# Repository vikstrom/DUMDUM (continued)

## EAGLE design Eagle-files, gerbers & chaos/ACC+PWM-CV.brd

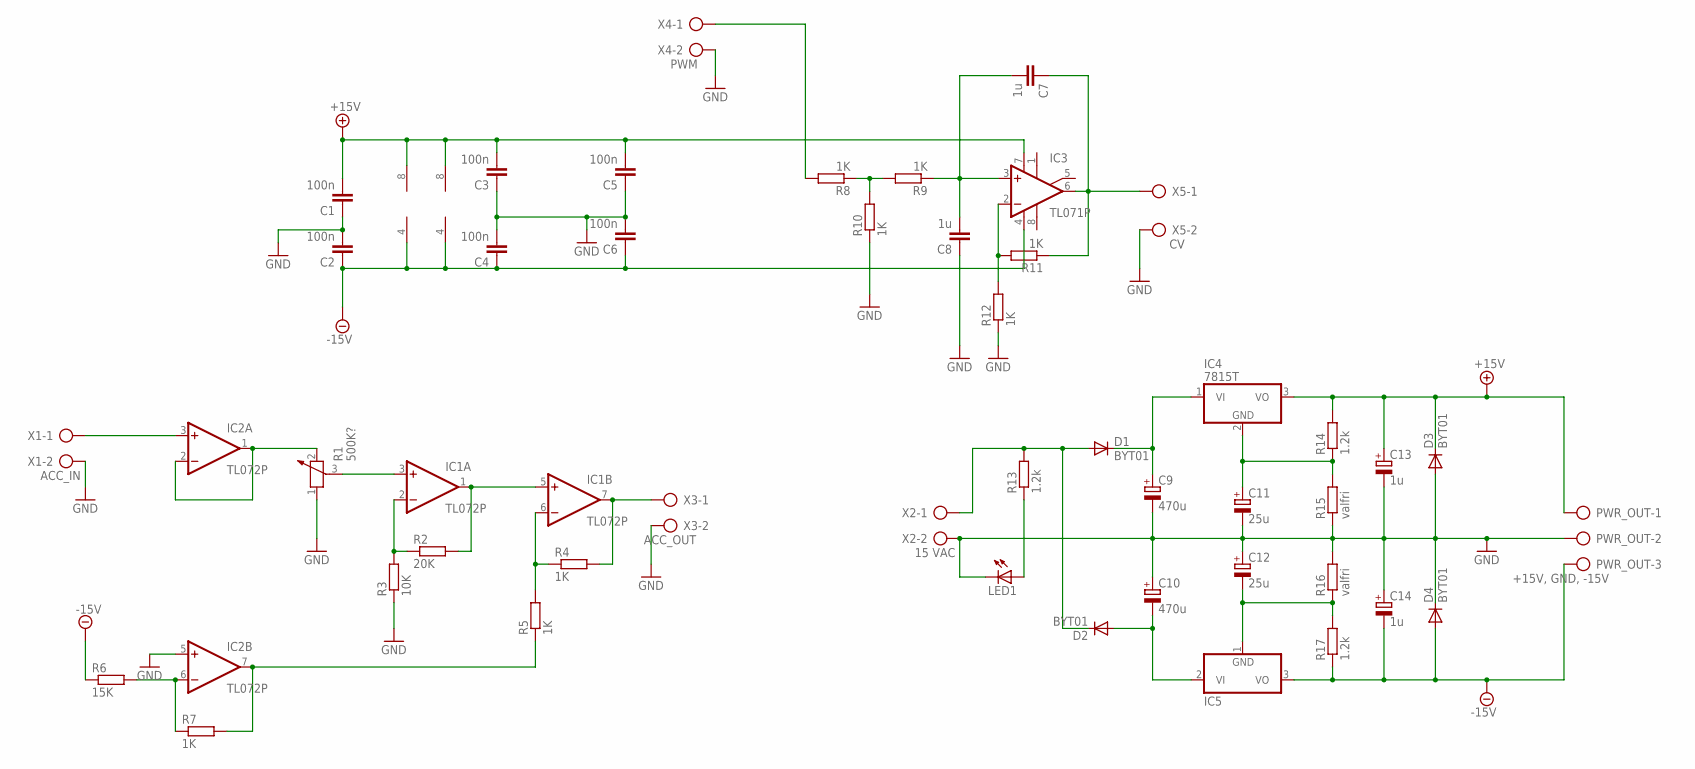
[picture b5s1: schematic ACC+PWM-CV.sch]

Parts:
C1, C2, C3, C4, C5, C6: 100n; C075-042X103
C7, C8: 1u; C075-042X103
C9, C10: 470u; E5-6
C11, C12: 25u; E5-6
C13, C14: 1u; E5-6
D1, D2, D3, D4: BYT01; F126-10
IC1, IC2: TL072P; DIL08
IC3: TL071P; DIL08
IC4: 7815T; TO220H
IC5: 7915T; TO220H
LED1: LED5MM
PWR_OUT: +15V, GND, -15V; AK300/3
R1: 500K?; PT-10
R2: 20K; 0207/10
R3: 10K; 0207/10
R4, R5, R7, R8, R9, R10, R11, R12: 1K; 0207/10
R6: 15K; 0207/10
R13, R14, R17: 1.2k; 0207/10
R15, R16: valfri; 0207/10
X1: ACC_IN; AK300/2
X2: 15 VAC; AK300/2
X3: ACC_OUT; AK300/2
X4: PWM; AK300/2
X5: CV; AK300/2

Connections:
+15V: C1.2, C3.2, C5.2, C13.+, D3.C, IC1.8 (V+), IC2.8 (V+), IC3.7 (V+), IC4.3 (VO), PWR_OUT.1, R14.2
-15V: C2.1, C4.1, C6.1, C14.-, D4.A, IC1.4 (V-), IC2.4 (V-), IC3.4 (V-), IC5.3 (VO), PWR_OUT.3, R6.1, R17.1
GND: C1.1, C2.2, C3.1, C4.2, C5.1, C6.2, C8.1, C9.-, C10.+, C11.-, C12.+, C13.-, C14.+, D3.A, D4.C, IC2.5 (+IN), LED1.K (C), PWR_OUT.2, R1.1, R3.1, R10.1, R12.1, R15.1, R16.2, X1.2, X2.2, X3.2, X4.2, X5.2
unnamed: IC2.1 (OUT), IC2.2 (-IN), R1.2
unnamed: IC1.3 (+IN), R1.3
unnamed: IC1.1 (OUT), IC1.5 (+IN), R2.2
unnamed: IC1.2 (-IN), R2.1, R3.2
unnamed: IC2.7 (OUT), R5.1, R7.2
unnamed: IC2.6 (-IN), R6.2, R7.1
unnamed: IC1.6 (-IN), R4.1, R5.2
unnamed: IC1.7 (OUT), R4.2, X3.1
unnamed: IC2.3 (+IN), X1.1
unnamed: R8.2, X4.1
unnamed: R8.1, R9.2, R10.2
unnamed: C7.2, C8.2, IC3.3 (+IN), R9.1
unnamed: C7.1, IC3.6 (OUT), R11.1, X5.1
unnamed: IC3.2 (-IN), R11.2, R12.2
unnamed: D1.A, D2.C, R13.2, X2.1
unnamed: LED1.A, R13.1
unnamed: C9.+, D1.C, IC4.1 (VI)
unnamed: C10.-, D2.A, IC5.2 (VI)
unnamed: C11.+, IC4.2 (GND), R14.1, R15.2
unnamed: C12.-, IC5.1 (GND), R16.1, R17.2

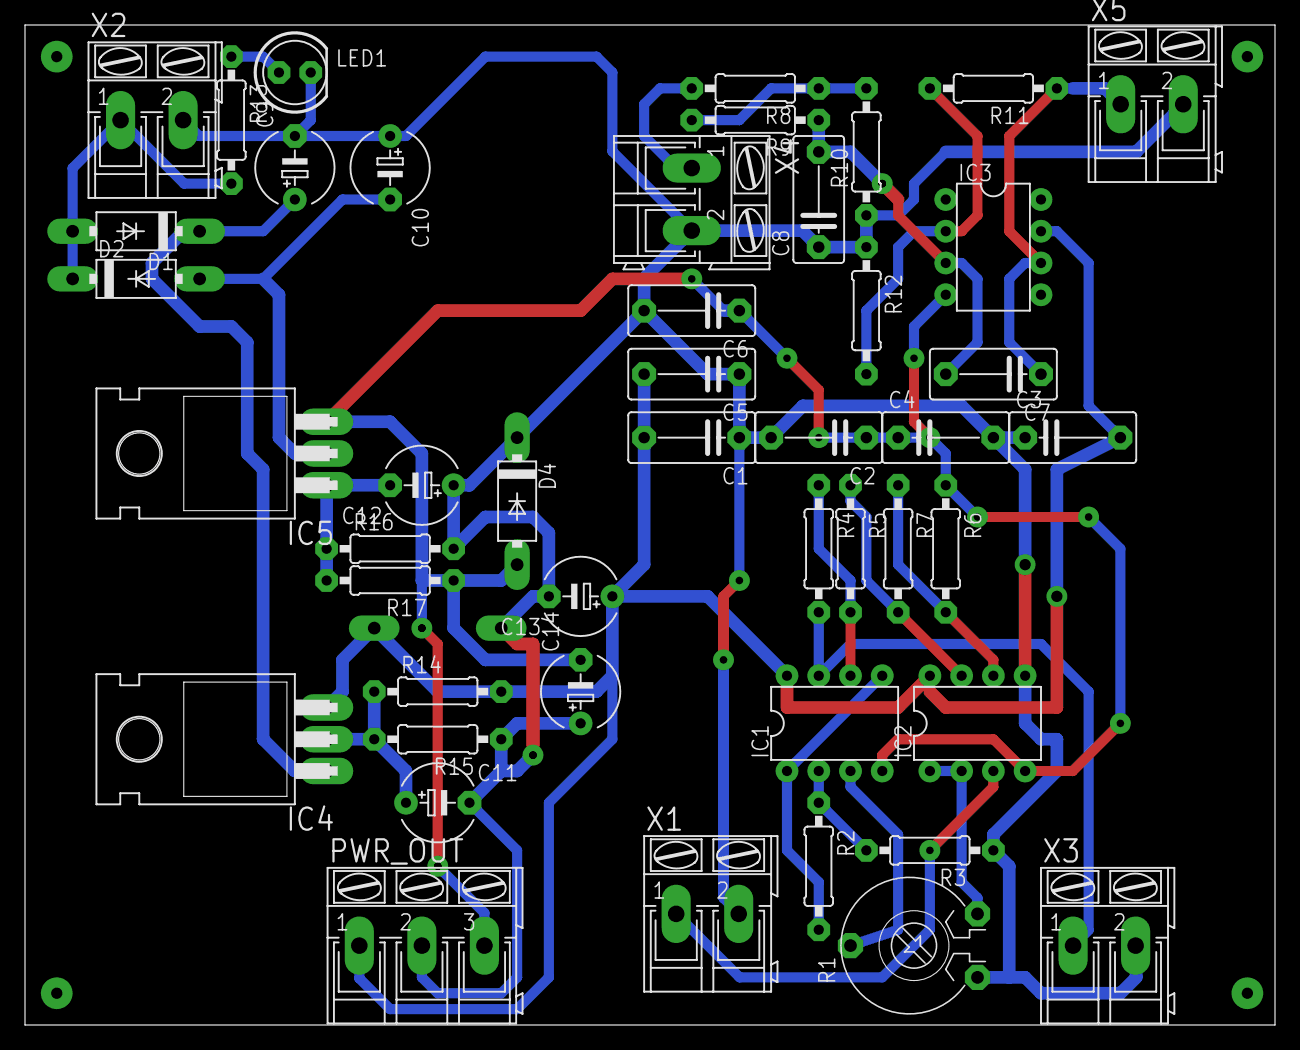
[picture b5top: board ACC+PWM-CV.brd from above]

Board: 2 copper layers, 100.0 x 80.0 mm, 47 parts (1 on the bottom side), 23 nets.

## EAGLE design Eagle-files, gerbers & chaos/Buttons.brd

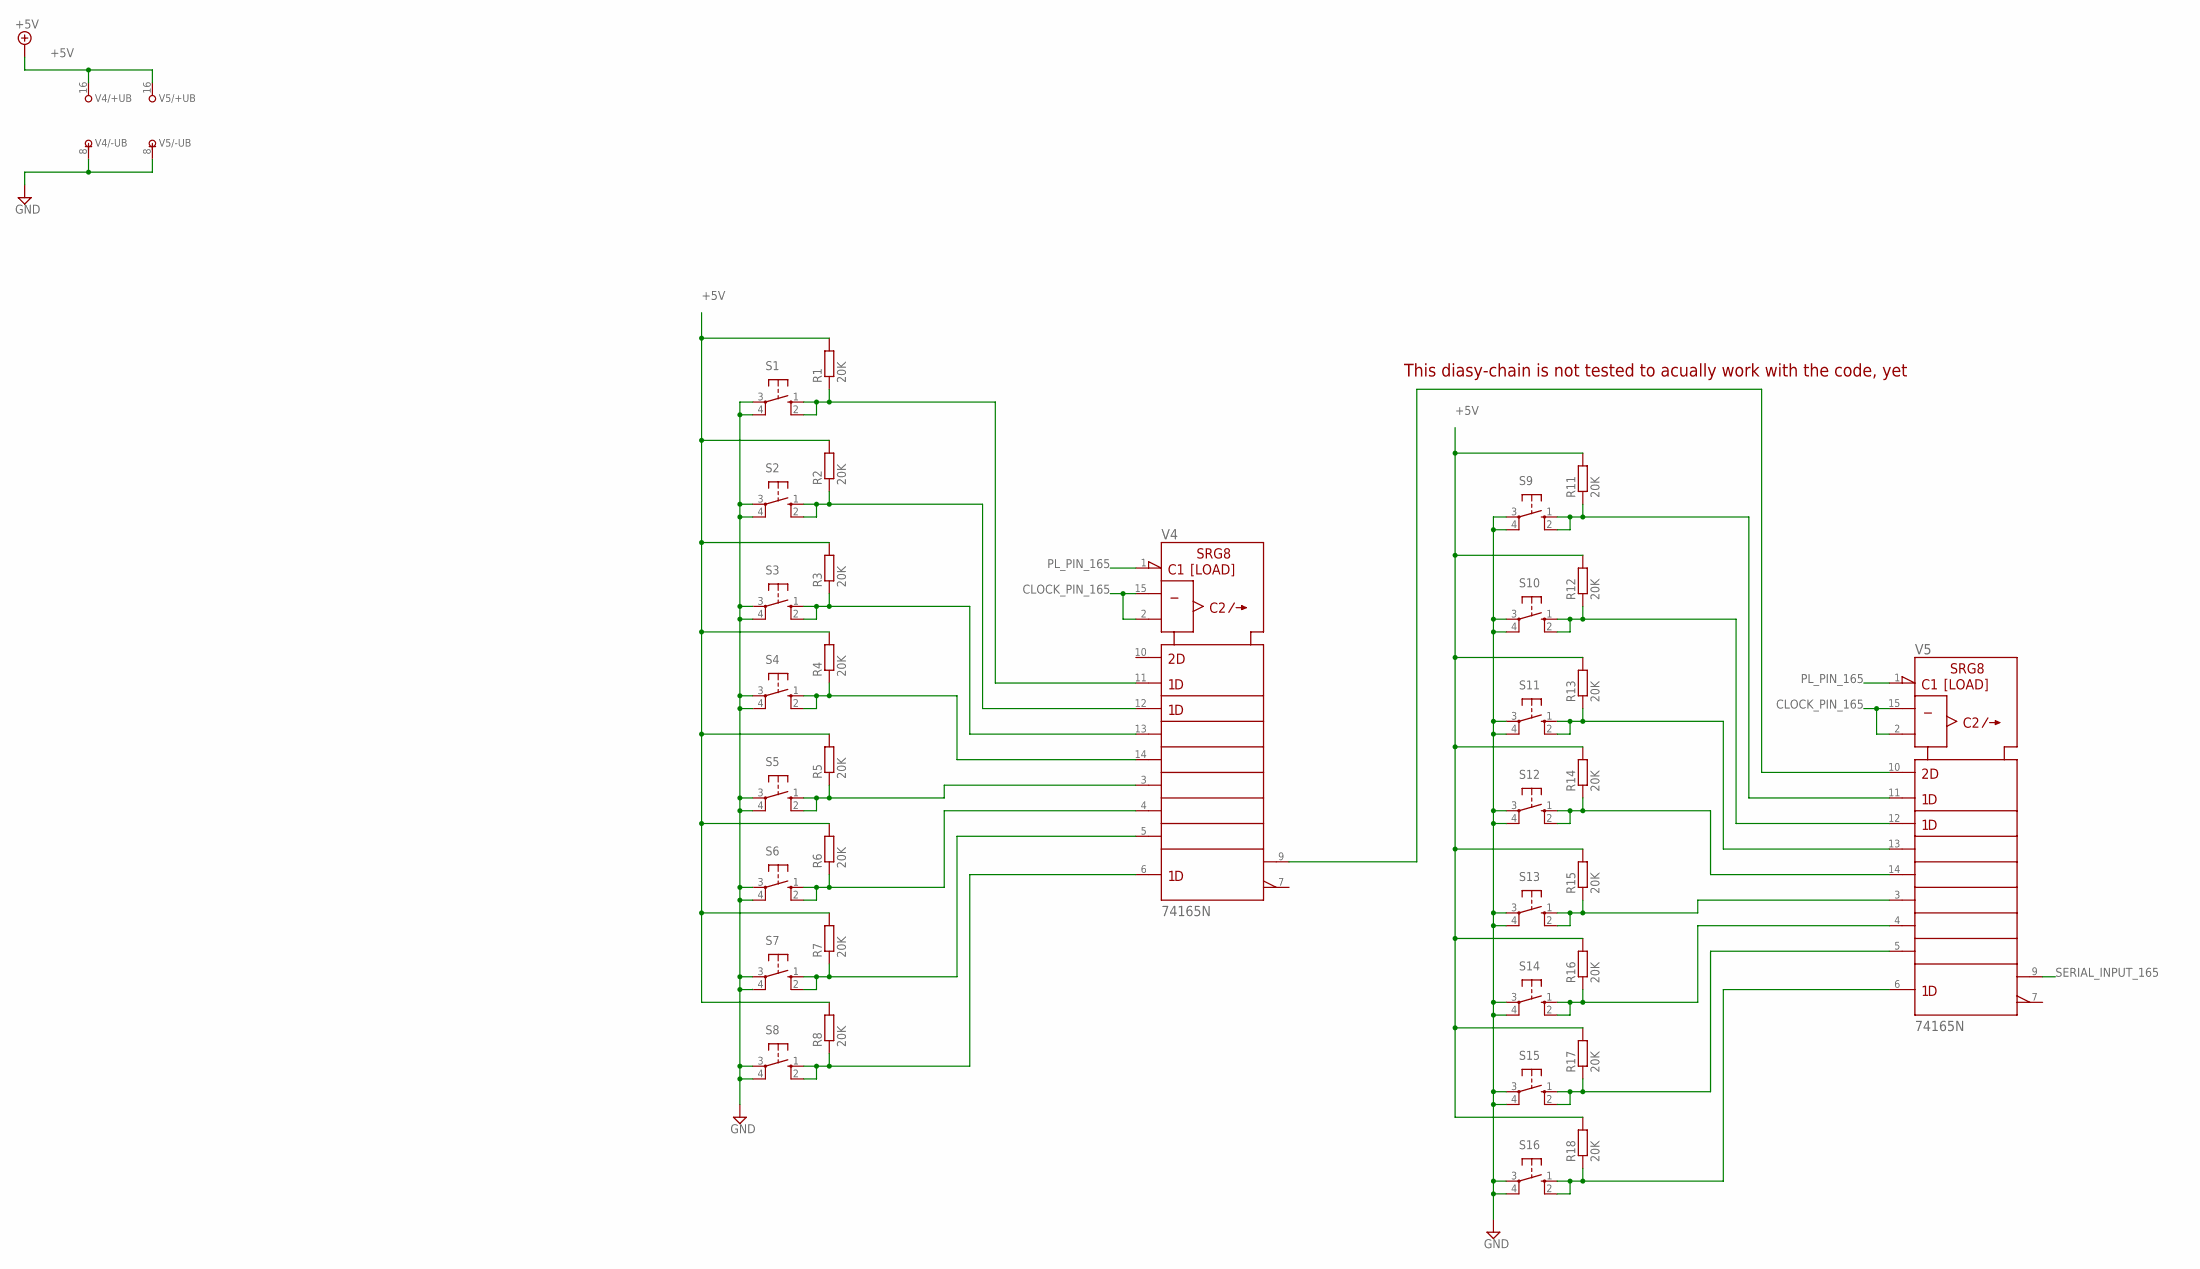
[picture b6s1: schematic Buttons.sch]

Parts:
R1, R2, R3, R4, R5, R6, R7, R8, R11, R12, R13, R14, R15, R16, R17, R18: 20K; 0204/7
S1, S2, S3, S4, S5, S6, S7, S8, S9, S10, S11, S12, S13, S14, S15, S16: 40-XX; B3F-40XX
V4, V5: 74165N; DIL16

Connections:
+5V: R1.2, R2.2, R3.2, R4.2, R5.2, R6.2, R7.2, R8.2, R11.2, R12.2, R13.2, R14.2, R15.2, R16.2, R17.2, R18.2, V4.16 (+UB), V5.16 (+UB)
CLOCK_PIN_165: V4.2 (CLK), V4.15 (CLK_INH), V5.2 (CLK), V5.15 (CLK_INH)
GND: S1.3, S1.4 (P1), S2.3, S2.4 (P1), S3.3, S3.4 (P1), S4.3, S4.4 (P1), S5.3, S5.4 (P1), S6.3, S6.4 (P1), S7.3, S7.4 (P1), S8.3, S8.4 (P1), S9.3, S9.4 (P1), S10.3, S10.4 (P1), S11.3, S11.4 (P1), S12.3, S12.4 (P1), S13.3, S13.4 (P1), S14.3, S14.4 (P1), S15.3, S15.4 (P1), S16.3, S16.4 (P1), V4.8 (-UB), V5.8 (-UB)
unnamed: R18.1, S16.1 (S), S16.2 (S1), V5.6 (H)
unnamed: R17.1, S15.1 (S), S15.2 (S1), V5.5 (G)
unnamed: R16.1, S14.1 (S), S14.2 (S1), V5.4 (F)
unnamed: R15.1, S13.1 (S), S13.2 (S1), V5.3 (E)
unnamed: R14.1, S12.1 (S), S12.2 (S1), V5.14 (D)
unnamed: R13.1, S11.1 (S), S11.2 (S1), V5.13 (C)
unnamed: R8.1, S8.1 (S), S8.2 (S1), V4.6 (H)
unnamed: R7.1, S7.1 (S), S7.2 (S1), V4.5 (G)
unnamed: R6.1, S6.1 (S), S6.2 (S1), V4.4 (F)
unnamed: R5.1, S5.1 (S), S5.2 (S1), V4.3 (E)
unnamed: R4.1, S4.1 (S), S4.2 (S1), V4.14 (D)
unnamed: R3.1, S3.1 (S), S3.2 (S1), V4.13 (C)
unnamed: R2.1, S2.1 (S), S2.2 (S1), V4.12 (B)
unnamed: R1.1, S1.1 (S), S1.2 (S1), V4.11 (A)
unnamed: R12.1, S10.1 (S), S10.2 (S1), V5.12 (B)
unnamed: R11.1, S9.1 (S), S9.2 (S1), V5.11 (A)
unnamed: V4.9 (QH), V5.10 (SER)
PL_PIN_165: V4.1 (SH/!LD), V5.1 (SH/!LD)
SERIAL_INPUT_165: V5.9 (QH)

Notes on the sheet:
This diasy-chain is not tested to acually work with the code, yet

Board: 2 copper layers, 34 parts (0 on the bottom side), 21 nets, no tracks yet.

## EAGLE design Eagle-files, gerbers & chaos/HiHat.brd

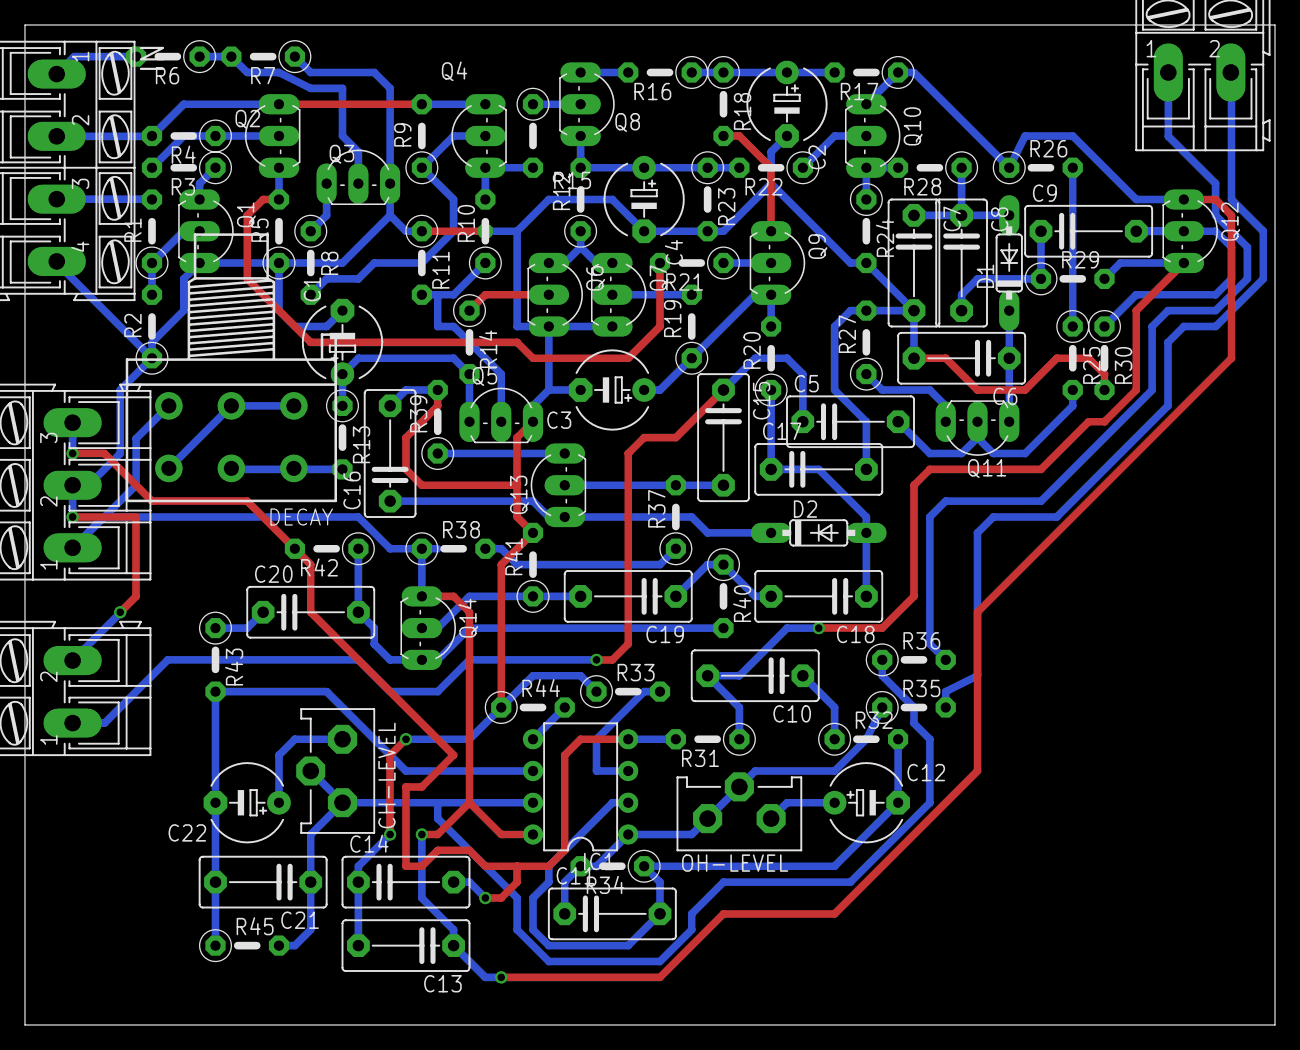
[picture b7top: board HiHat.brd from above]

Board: 2 copper layers, 100.0 x 80.0 mm, 91 parts (0 on the bottom side), 59 nets.

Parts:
C1: 10u/16v; E5-6
C2: 47u/16v; E5-6
C3, C4: 0.47u; E5-6
C5, C15: 22n; C075-042X103
C6, C7, C8, C9, C16, C17, C18, C19: 1.5n; C075-042X103
C10, C20: 470p; C075-042X103
C11, C21: 220p; C075-042X103
C12, C22: 33u/6.3v; E5-6
C13, C14: 0.1u; C075-042X103
CH-LEVEL: 100k; ECP10P
D1, D2: 1N4148; DO35-7
DECAY: 1M; 3RP/1610G
IC1: TL072P; DIL08
IN: OH-TRIG, ACC, CH-TRIG; AK300/4
NOISE: AK300/2
OH-LEVEL: 100k; ECP10P
OUT: AK300/2
PWR: +15V, GND, -15V; AK300/3
Q1, Q3, Q5, Q6, Q7, Q8, Q9, Q10, Q11, Q12, Q13, Q14: BC546A; TO92-EBC
Q2, Q4: BC556A; TO92-EBC
R1, R3, R5, R6, R8, R10, R31, R42: 22k; 0207/5V
R2, R7, R11, R14, R15: 10k; 0207/5V
R4, R9: 4.7k; 0207/5V
R12, R13: 100k; 0207/5V
R16, R18: 470; 0207/5V
R17, R27, R39: 100; 0207/5V
R19: 330k; 0207/5V
R20, R21, R22, R24, R28: 33k; 0207/5V
R23, R25, R26, R37, R38: 1M; 0207/5V
R29, R40: 2.7k; 0207/5V
R30, R41: 69k; 0207/5V
R32, R43: 39k; 0207/5V
R33, R44: 47k; 0207/5V
R34, R45: 470k; 0207/5V
R35, R36: 1k; 0207/5V

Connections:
+15V: C13.1, DECAY.1-3, IC1.8, PWR.1, Q10.C, Q12.C, Q14.C, R17.1, R26.1, R38.1
-15V: C14.2, IC1.4, PWR.3, R31.2, R42.2
GND: C1.-, C2.-, C3.-, C4.-, C6.2, C7.2, C13.2, C14.1, C16.2, C17.2, IN.4, NOISE.2, PWR.2, Q1.E, Q3.E, Q5.E, Q6.E, Q7.E, R2.1, R5.1, R7.1, R11.1, R23.2, R24.2, R27.2, R30.2, R33.1, R39.2, R41.2, R44.1
unnamed: IN.3, R1.2
unnamed: Q1.B, R1.1, R2.2
unnamed: IN.2, Q2.E, Q4.E, R4.2, R9.2
unnamed: Q2.B, R3.2, R4.1
unnamed: Q1.C, R3.1
unnamed: Q3.B, R6.1, R7.2
unnamed: Q2.C, R5.2, R21.2
unnamed: IN.1, R6.2
unnamed: Q3.C, R8.1
unnamed: Q5.B, R10.1, R11.2
unnamed: Q4.B, R8.2, R9.1
unnamed: Q4.C, R10.2, R15.2
unnamed: DECAY.1-1, DECAY.1-2, DECAY.2-3
unnamed: Q6.B, R14.1
unnamed: Q8.B, R15.1
unnamed: C2.+, R16.1, R17.2, R18.1
unnamed: C1.+, Q5.C, R13.1, R14.2
unnamed: C4.+, Q8.E, R12.2, R22.2, R23.1
unnamed: Q6.C, Q7.C, R12.1
unnamed: Q8.C, R16.2
unnamed: Q7.B, R19.2
unnamed: C3.+, Q9.E, R19.1, R20.2
unnamed: R25.1, R26.2
unnamed: Q9.B, R21.1
unnamed: C5.2, Q11.B, R25.2
unnamed: Q9.C, R18.2
unnamed: Q10.B, R22.1
unnamed: Q10.E, R24.1, R28.2
unnamed: Q11.E, R27.1
unnamed: C6.1, D1.C, Q11.C
unnamed: C7.1, C8.1, D1.A, R28.1
unnamed: C11.2, C12.-, IC1.2, R32.2, R34.1
unnamed: C8.2, C9.1, R29.1
unnamed: C9.2, Q12.B, R30.1
unnamed: C10.2, Q12.E, R29.2, R31.1
unnamed: C10.1, R32.1
unnamed: IC1.3, R33.2
unnamed: OUT.2, R35.2
unnamed: C12.+, OH-LEVEL.E
unnamed: C11.1, IC1.1, OH-LEVEL.A, OH-LEVEL.S, R34.2, R35.1
unnamed: R37.1, R38.2
unnamed: C15.2, Q13.B, R37.2
unnamed: Q13.E, R39.1
unnamed: C16.1, D2.C, Q13.C
unnamed: C17.1, C18.1, D2.A, R20.1
unnamed: C18.2, C19.1, R40.1
unnamed: C19.2, Q14.B, R41.1
unnamed: C20.2, Q14.E, R40.2, R42.1
unnamed: C20.1, R43.1
unnamed: C5.1, C15.1, NOISE.1
unnamed: C21.2, C22.-, IC1.6, R43.2, R45.1
unnamed: C22.+, CH-LEVEL.E
unnamed: C21.1, CH-LEVEL.A, CH-LEVEL.S, IC1.7, R36.1, R45.2
unnamed: IC1.5, R44.2
unnamed: OUT.1, R36.2
unnamed: DECAY.2-1, DECAY.2-2, R13.2

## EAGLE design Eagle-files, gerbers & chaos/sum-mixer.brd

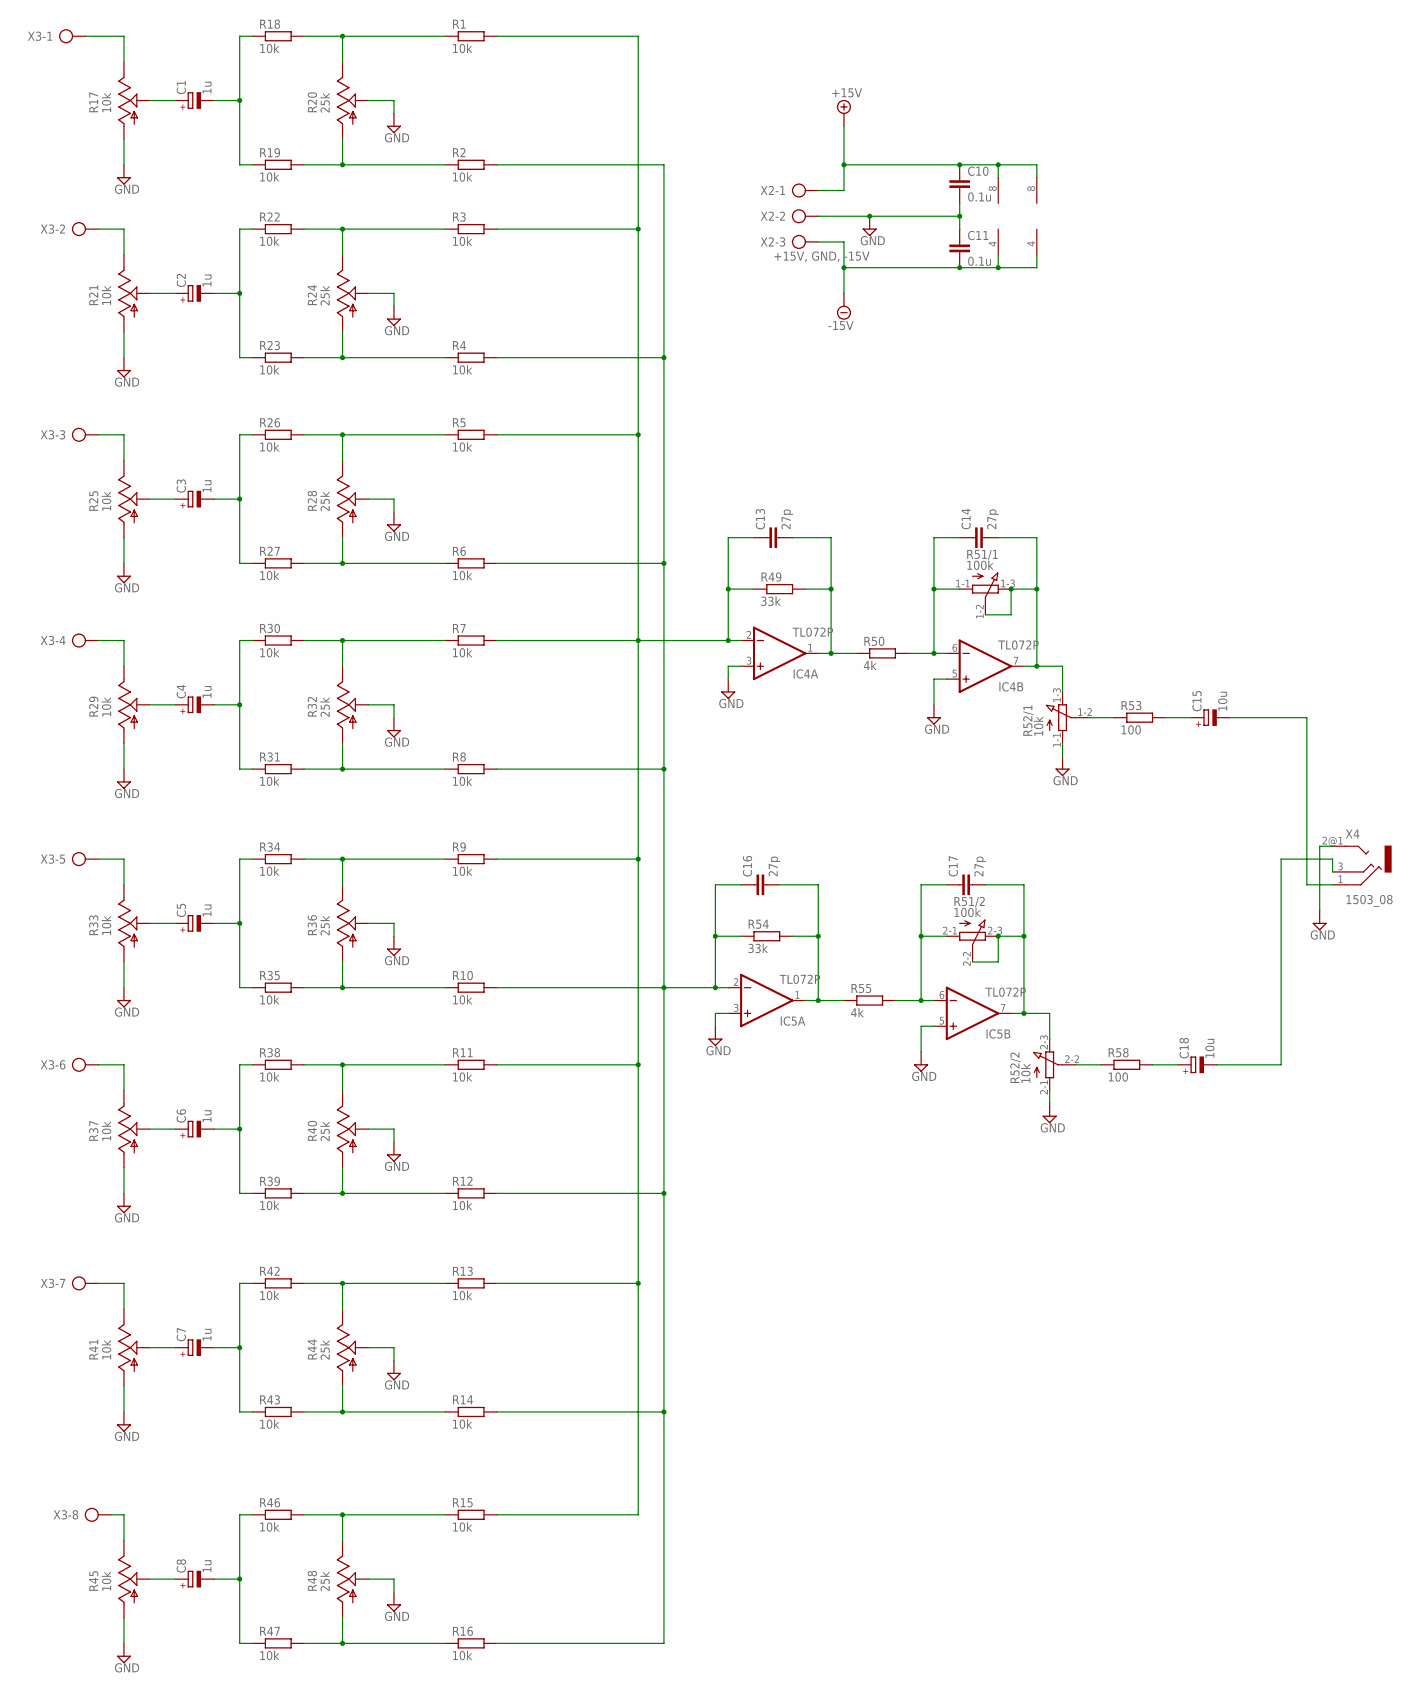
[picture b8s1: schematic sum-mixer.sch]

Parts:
C1, C2, C3, C4, C5, C6, C7, C8: 1u; E5-6
C10, C11: 0.1u; C075-042X103
C13, C14, C16, C17: 27p; C025-024X044
C15, C18: 10u; E5-6
IC4, IC5: TL072P; DIL08
R1, R2, R3, R4, R5, R6, R7, R8, R9, R10, R11, R12, R13, R14, R15, R16, R18, R19, R22, R23, R26, R27, R30, R31, R34, R35, R38, R39, R42, R43, R46, R47: 10k; 0207/5V
R17, R21, R25, R29, R33, R37, R41, R45: 10k; B25P
R20, R24, R28, R32, R36, R40, R44, R48: 25k; B25P
R49, R54: 33k; 0207/5V
R50, R55: 4k; 0207/5V
R51: 100k; 3RP/1610G
R52: 10k; 3RP/1610G
R53, R58: 100; 0207/5V
X2: +15V, GND, -15V; AK300/3
X3: AK300/8
X4: 1503_08

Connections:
+15V: C10.1, IC4.8 (V+), IC5.8 (V+), X2.1
-15V: C11.2, IC4.4 (V-), IC5.4 (V-), X2.3
GND: C10.2, C11.1, IC4.3 (+IN), IC4.5 (+IN), IC5.3 (+IN), IC5.5 (+IN), R17.A, R20.S, R21.A, R24.S, R25.A, R28.S, R29.A, R32.S, R33.A, R36.S, R37.A, R40.S, R41.A, R44.S, R45.A, R48.S, R52.1-1 (A), R52.2-1 (A), X2.2, X4.2@1 (2)
unnamed: R1.1, R18.2, R20.E
unnamed: R2.1, R19.2, R20.A
unnamed: R3.1, R22.2, R24.E
unnamed: R4.1, R23.2, R24.A
unnamed: R5.1, R26.2, R28.E
unnamed: R6.1, R27.2, R28.A
unnamed: R7.1, R30.2, R32.E
unnamed: R8.1, R31.2, R32.A
unnamed: R9.1, R34.2, R36.E
unnamed: R10.1, R35.2, R36.A
unnamed: R11.1, R38.2, R40.E
unnamed: R12.1, R39.2, R40.A
unnamed: R13.1, R42.2, R44.E
unnamed: R14.1, R43.2, R44.A
unnamed: R15.1, R46.2, R48.E
unnamed: R16.1, R47.2, R48.A
unnamed: C1.+, R17.S
unnamed: C2.+, R21.S
unnamed: C3.+, R25.S
unnamed: C1.-, R18.1, R19.1
unnamed: C4.+, R29.S
unnamed: C5.+, R33.S
unnamed: R17.E, X3.1
unnamed: C2.-, R22.1, R23.1
unnamed: C6.+, R37.S
unnamed: C7.+, R41.S
unnamed: R21.E, X3.2
unnamed: C3.-, R26.1, R27.1
unnamed: C8.+, R45.S
unnamed: R25.E, X3.3
unnamed: C4.-, R30.1, R31.1
unnamed: R29.E, X3.4
unnamed: C5.-, R34.1, R35.1
unnamed: R33.E, X3.5
unnamed: C6.-, R38.1, R39.1
unnamed: R37.E, X3.6
unnamed: C7.-, R42.1, R43.1
unnamed: R41.E, X3.7
unnamed: C8.-, R46.1, R47.1
unnamed: C16.1, IC5.2 (-IN), R2.2, R4.2, R6.2, R8.2, R10.2, R12.2, R14.2, R16.2, R54.1
unnamed: C13.1, IC4.2 (-IN), R1.2, R3.2, R5.2, R7.2, R9.2, R11.2, R13.2, R15.2, R49.1
unnamed: R45.E, X3.8
unnamed: C13.2, IC4.1 (OUT), R49.2, R50.1
unnamed: C14.1, IC4.6 (-IN), R50.2, R51.1-1 (A)
unnamed: C14.2, IC4.7 (OUT), R51.1-2 (S), R51.1-3 (E), R52.1-3 (E)
unnamed: R52.1-2 (S), R53.1
unnamed: C15.+, R53.2
unnamed: C18.-, X4.3
unnamed: C16.2, IC5.1 (OUT), R54.2, R55.1
unnamed: C17.1, IC5.6 (-IN), R51.2-1 (A), R55.2
unnamed: C17.2, IC5.7 (OUT), R51.2-2 (S), R51.2-3 (E), R52.2-3 (E)
unnamed: R52.2-2 (S), R58.1
unnamed: C18.+, R58.2
unnamed: C15.-, X4.1

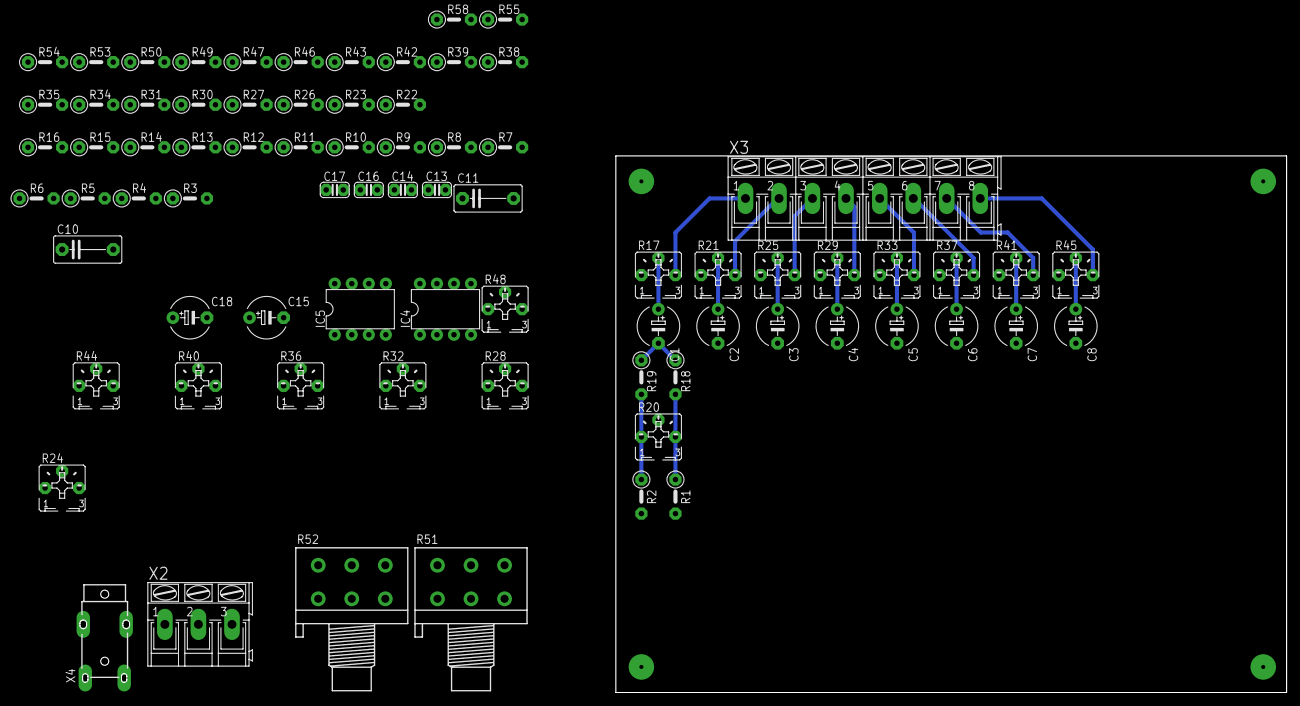
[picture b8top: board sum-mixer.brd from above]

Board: 2 copper layers, 77 parts (0 on the bottom side), 57 nets.

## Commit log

2014-02-28 Added schematics and PCB
2014-02-28 Cleaned up the directory
2014-02-28 Circuits and code gathered
2014-02-28 nuffin special
2014-02-28 Added tap tempo test
2014-03-04 worked on buttoncheck
2014-03-04 workingBranch created, new code added and cleaned
2014-03-05 fixed minor typo
2014-03-05 clean-up before bed
2014-03-09 Have begun to integrate 7seg-display into main-program
2014-03-09 Changed BPM calculation
2014-03-10 Fised integer division-problem with the bpm calulation
2014-03-11 test branch
2014-03-11 Fixed BPM calculation
2014-03-11 Added 7seg&buttons schematics
2014-03-11 7sge&buttons schematics finnished
2014-03-19 Minor update in tempoDisplay
2014-03-20 Should work for 3x7seg display
2014-04-02 separated display-pcb and button-pcb
2014-04-02 7seg-pcb should be finnished, also changed text in power-pcb
2014-05-11 Started putting all test-programs togheter
2014-05-12 putting it all togheter in V3
2014-05-13 Cleaned a bit
2014-05-13 Added playArray with digitalWrite control
2014-05-13 play output is now controlled via a 595
2014-05-20 added digitalWriteFast
2015-03-25 Cleaned up, added PDF of schematics
